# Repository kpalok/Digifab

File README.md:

This is our repository for the files included in Cat food dispenser project.
Documetation and diary can be found in the link above or in gh-pages branch.

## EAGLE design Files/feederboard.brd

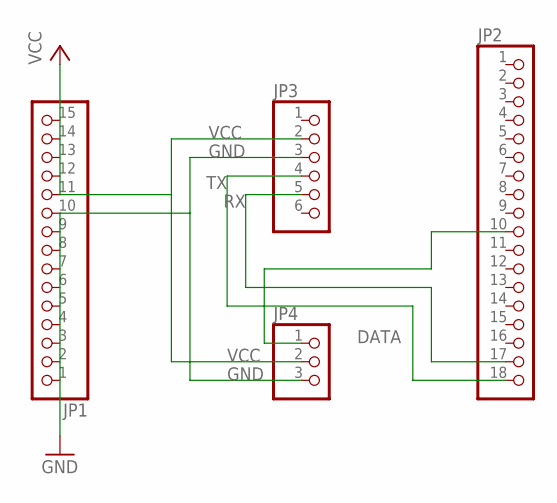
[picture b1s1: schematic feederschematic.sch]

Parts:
JP1: PINHD-1X15; 1X15
JP2: PINHD-1X18; 1X18
JP3: PINHD-1X6; 1X06
JP4: PINHD-1X3; 1X03

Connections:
DATA: JP2.10, JP4.1
GND: JP1.10, JP3.3, JP4.3
RX: JP2.17, JP3.5
TX: JP2.18, JP3.4
VCC: JP1.11, JP3.2, JP4.2

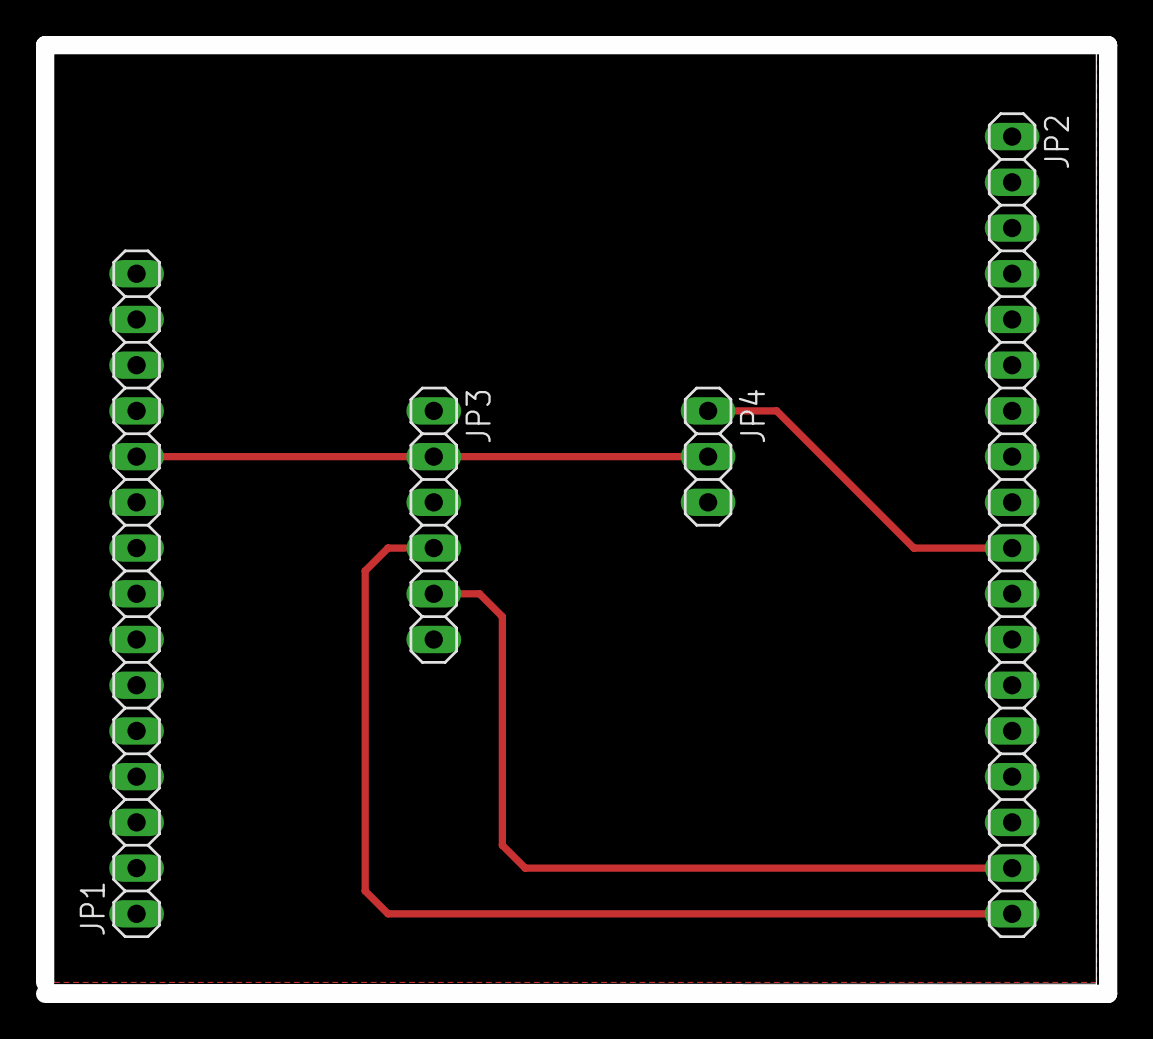
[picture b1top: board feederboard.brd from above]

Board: 2 copper layers, 59.1 x 52.7 mm, 4 parts (0 on the bottom side), 5 nets.

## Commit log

2018-03-20 Set theme jekyll-theme-minimal
2018-03-20 Update README.md
    alkutestailua
2018-03-20 Create testiboi
2018-03-20 Create Week 1
2018-03-20 Update Week 1
2018-04-04 Lisää .gitignore ja Scetch.pdf
2018-04-04 Add Scetch.JPG, delete Scetch.pdf
2018-04-04 Set theme jekyll-theme-slate
2018-04-04 Add Images folder and two scetches
2018-04-04 Fix typos
2018-04-12 Add index.md
2018-04-12 Add 2018-04-12-Weekly-report.md
2018-04-12 Update index.md
    Testing out links
2018-04-12 Rename 2018-04-12-Weekly-report.md to 2018-04-12-weekly-report.md
2018-04-12 Rename 2018-4-4-Weekly-report.md to 2018-04-04-weekly-report.md
2018-04-13 Update 2018-04-04-weekly-report.md
    Fixed title
2018-04-13 Add files via upload
    Added source code files
2018-04-13 Update 2018-04-12-weekly-report.md
    Personal commit to diary.
2018-04-13 Update index.md
    Added bullets
2018-04-15 Update index.md
    Added link for week 1
2018-04-15 Add _includes folder and youtubePlayer.html
2018-04-15 Update 2018-04-12-weekly-report.md
    Desperate attempt to embed a YouTube video
2018-04-15 Add files via upload
    Update
2018-04-15 Removed app directory
2018-04-15 Add files via upload
    I did something stupid and "fixed" it.
2018-04-17 Update index.md
    Updated the links
2018-04-17 Update 2018-04-12-weekly-report.md
    Things have been done and those things have been reported in a proper manner
2018-04-17 Add files via upload
    Nykyinen katajaan kapsahtanut tilanne.
2018-04-18 Add files via upload
    Could be getting somewhere.
2018-04-19 Update index.md
    :-D
2018-04-19 Remove posts
2018-04-19 remove
2018-04-19 Remove FeederApp folder
2018-04-20 Update 2018-04-16-weekly-report.md
    Addition
2018-04-20 Add Container Render
2018-04-20 Delete Container Render
    Nvm wrong branch
2018-04-20 Add ContainerRender.png
2018-04-23 Added .apk file
2018-04-23 begun to completely rework bluetoothservice, app currently not in working form.
2018-04-24 new test apk
2018-04-24 test
2018-04-24 test2
2018-04-24 Removed bluetooth connection within the app to maybe get it working
2018-04-24 An exiting change in bluetooth connection progress
2018-04-24 Small updato to last
2018-04-25 trials
2018-04-25 new apk
2018-04-25 new apk 2.2
2018-04-25 apk 2.2
2018-04-25 Updated functionality, migh actually work soon!!
2018-04-25 Implemented instanse saving
2018-04-26 Actually working
2018-04-27 added arduino code
2018-04-27 Added loop to .connect()
2018-04-27 removed unnecessary loop
2018-04-27 Update README.txt
    Added some information about the app.
2018-05-02 Update index.md
    Added a link for the new weekly report
2018-05-02 Add images from ProtoBooth
2018-05-02 Add files folder and a few project files
2018-05-02 Rotate images
2018-05-02 Add BluetoothDemo.gif
2018-05-02 Update 2018-05-02-weekly-report.md
    There was an attempt to show a gif
2018-05-02 Update 2018-05-02-weekly-report.md
    A successful attempt
2018-05-03 Update ServoActivity.ino
    update
2018-05-03 Update 2018-04-25-weekly-report.md
    Wrote a story about the app
2018-05-03 Update 2018-04-16-weekly-report.md
    Resized the ContainerRender.png image
2018-05-03 Update 2018-03-26-weekly-report.md
    An attempt
2018-05-03 Update 2018-03-26-weekly-report.md
    Another one
2018-05-03 Update 2018-04-04-weekly-report.md
    And another one
2018-05-03 Update 2018-04-12-weekly-report.md
    Aand another one
2018-05-03 Update 2018-04-16-weekly-report.md
    Aaand another one
2018-05-03 Update 2018-04-25-weekly-report.md
    Aaaand another one
2018-05-03 Update 2018-05-02-weekly-report.md
    And anotha one
2018-05-04 modified servoactivity
2018-05-06 Rename STL-files
    Changed the names to something more descriptive
2018-05-06 Add images and gifs
2018-05-07 Delete ServoActivity.ino
    delete copy
2018-05-07 Delete Images folder
    ...again
2018-05-07 Add Prototype.JPG
2018-05-08 Update BluetoothFeedService.cs
    Removed unnecessary logging.
2018-05-08 Fixed typo
